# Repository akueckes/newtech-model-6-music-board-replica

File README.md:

# Welcome to another replica project for the Newtech Model 6 Music Board

The Model 6 Music Board from Newtech Computer Systems was launched in 1977 as a low cost alternative to other,
more expensive sound solutions for the S-100 bus like the D+7A from Cromemco.
In contrast to the D+7A with its up to seven bidirectional analog channels, the Newtech board implements just a single audio output channel
and does not provide input channels for e.g. connecting joysticks or keyboards.

The minimalistic design was based on a simple bus interface with address decoder,
a digital to analog converter (DAC) built by a six-step resistor ladder, and a single LM380 IC as simple low power amplifier.

The Music Board can be equipped with a single 2" speaker, or connected to an external amplifier via a phono jack.
Multiple boards can be combined for stereo output.

An optional daughter board can be added to improve the audio quality by an active low pass filter.

Due to the simplistic design, audio generation is achieved by directly and continuously driving the
DAC by the CPU with a constant rate, producing a wave output.
Although this keeps the CPU busy from doing other things, there are no limits concerning the type of audio output.
Music can be produced as well as arbitrary sounds, including human speech or noise.
Multiple voices can be mixed into a single channel, which is then output via the hardware.
Synthesis is just a matter of software, and primarily limited by the performance of the CPU.
Assembler programming, however, is mandatory in order to feed a continuous stream of 6-bit audio samples into the board.

This repository contains the replica KiCAD files for both the Music Board and the low pass filter PCB.
Please consult the Newtech User Manual for a parts list / bill of material.

There are other great replica projects around. The aim of this project is to be as close as possible to the original hardware.
Just a few components need to be added in order to build your own working sound solution for your S-100 based system.

Just as a reference, here is a sample picture of the original hardware without low pass filter

And here a picture of the replica, again without low pass filter, built up with components close to the original

Note that the bus contact fingers of the replica are not gold plated as the original.
Gold plating is a process which needs to be negotiated directly with the PCB producer of your choice and can't be specified by a directive in the Gerber files.

The replica is a nice little project requiring limited budget and skills to create your first own hardware for your personal S-100 system.

This by the way is the very first version of the replica design, please feel free to comment on any kind of improvement,
as long as the replica itself stays as close as possible to the original. A couple of limitations are intentional, so there is for instance
no solder mask in the Gerbers, and no jumper for activating/deactivating the internal speaker,
and as with the original, the low pass filter needs to be added with a daughter board
and is intentionally not integrated into the board design as with other replicas.

For your convenience, a copy of the original Model 6 Music Board user manual is provided,
as well as a BDOS based audio test program I once have written for diverse sound solutions for the S-100 bus,
which also supports up to two Newtech Model 6 Music Boards in parallel. I have created some kind of notation
for playing music scores with multiple channels, an example is the file FANFAR, which works with two boards configured at ports 24H and 28H.
STRINGS and TRUMPS are example wave files which can be loaded for different types of instrumentation.

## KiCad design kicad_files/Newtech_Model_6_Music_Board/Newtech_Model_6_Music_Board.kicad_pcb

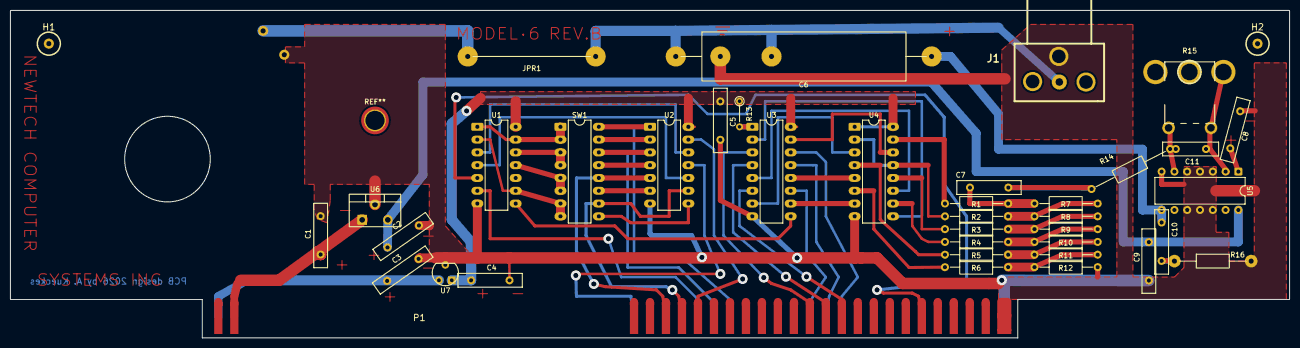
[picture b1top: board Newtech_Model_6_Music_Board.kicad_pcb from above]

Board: 2 copper layers, 254.0 x 65.0 mm, 41 parts (0 on the bottom side), 56 nets.

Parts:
C1, C2, C3: 1uF; C_Disc_D10.0mm_W2.5mm_P300mil
C4, C5, C9, C10: .1; C_Disc_D10.0mm_W2.5mm_P300mil
C6: 220; C_Axial_L22.0mm_D9.5mm_P27.50mm_Horizontal
C7: .1; C_Disc_D10.0mm_W2.5mm_P5.00mm
C8: 4.7; C_Disc_D10.0mm_W2.5mm_P300mil
C11: .0022; C_Disc_D10.0mm_W2.5mm_P6.0mm
H1, H2, H3: Ejector; s100-ejector
J1: RCA_audio_jack
JPR1: R_Axial_DIN0207_L6.3mm_D2.5mm_P15.24mm_Horizontal
P1: S100_MALE
R1, R2, R3, R4, R5, R6: 20K; R_Axial_DIN0207_L6.3mm_D2.5mm_P12.70mm_Horizontal
R7, R8, R9, R10, R11, R12: 10K; R_Axial_DIN0207_L6.3mm_D2.5mm_P12.70mm_Horizontal
R13: 4.7K; R_Axial_DIN0204_L3.6mm_D1.6mm_P5.08mm_Vertical
R14: 2M; R_Axial_DIN0207_L6.3mm_D2.5mm_P15.24mm_Horizontal
R15: 25K; Bourns_3355
R16: 1; R_Axial_DIN0207_L6.3mm_D2.5mm_P15.24mm_Horizontal
SW1: SW_DIP_x08; CERDIP-16_W7.62mm_SideBrazed_LongPads
U1: 74LS30; DIP-14_W7.62mm_LongPads
U2: 74LS04; DIP-14_W7.62mm_LongPads
U3: 74LS174; CERDIP-16_W7.62mm_SideBrazed_LongPads
U4: 4050; CERDIP-16_W7.62mm_SideBrazed_LongPads
U5: LM380N; DIP-14_W7.62mm
U6: LM7812_TO220; TO-220-3_Vertical
U7: L78L05_TO92; TO-92_Inline

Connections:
+8V: C3.1, P1.1 (+8_V), P1.51 (+8_V), U7.3 (VI)
+12V: C2.1, C9.1, U5.14 (VS), U6.3 (VO)
+16V: C1.1, P1.2 (+16_V), U6.1 (VI)
/I/O Enable: U1.8, U3.9 (Cp)
A2: P1.81 (A2), U1.6
A3: P1.31 (A3), U2.13
A4: P1.30 (A4), SW1.10, U2.9
A5: P1.29 (A5), SW1.12, U2.5
A6: P1.82 (A6), SW1.14, U2.3
A7: P1.83 (A7), SW1.16, U2.1
DO2: P1.88 (DO2_ED2), U3.11 (D3)
DO3: P1.89 (DO3_ED3), U3.13 (D4)
DO4: P1.38 (DO4_ED4), U3.3 (D0)
DO5: P1.39 (DO5_ED5), U3.4 (D1)
DO6: P1.40 (DO6_ED6), U3.6 (D2)
DO7: P1.90 (DO7_ED7), U3.14 (D5)
GND: C1.2, C2.2, C3.2, C4.2, C5.2, C8.2, C9.2, J1.2 (Ext), P1.50 (0_V2), P1.100 (0_V5), R12.1, R16.2, U1.7 (GND), U2.7 (GND), U3.8 (GND), U4.8 (VSS), U5.3 (GND), U5.4 (GND), U5.5 (GND), U5.7 (GND), U5.10 (GND), U5.11 (GND), U5.12 (GND), U6.2 (GND), U7.2 (GND)
unnamed: C7.1, R1.1, R7.2
unnamed: C7.2, R14.2
unnamed: C10.1, R16.1
unnamed: C6.1, C10.2, U5.8
unnamed: C6.2, J1.1 (In), JPR1.1 (A)
unnamed: R1.2, U4.15
unnamed: R2.1, R7.1, R8.2
unnamed: R2.2, U4.2
unnamed: R3.1, R8.1, R9.2
unnamed: R3.2, U4.12
unnamed: R4.2, U4.10
unnamed: R5.2, U4.4
unnamed: R6.2, U4.6
unnamed: R5.1, R10.1, R11.2
unnamed: R4.1, R9.1, R10.2
unnamed: R6.1, R11.1, R12.2
unnamed: SW1.1, SW1.2, U1.1, U1.13
unnamed: SW1.3, SW1.4, U1.12
unnamed: SW1.5, SW1.6, U1.11
unnamed: SW1.7, SW1.8, U1.2, U1.9
unnamed: SW1.9, U2.8
unnamed: SW1.11, U2.6
unnamed: SW1.13, U2.4
unnamed: SW1.15, U2.2
unnamed: U1.3, U2.12
unnamed: U1.4, U2.10
unnamed: U3.2 (Q0), U4.9
unnamed: U3.5 (Q1), U4.11
unnamed: U3.7 (Q2), U4.3
unnamed: U3.10 (Q3), U4.7
unnamed: U3.12 (Q4), U4.5
unnamed: U3.15 (Q5), U4.14
unnamed: R13.2, U3.1 (~Mr)
unnamed: C11.2, R15.1, R15.2, U5.2 (+)
unnamed: C11.1, R14.1, R15.3, U5.6 (-)
unnamed: C8.1, U5.1 (BYPASS)
PWR/: P1.77 (pWR*), U2.11
SOUT: P1.45 (sOUT), U1.5
VCC: C4.1, C5.1, R13.1, U1.14 (VCC), U2.14 (VCC), U3.16 (VCC), U4.1 (VCC), U4.16, U7.1 (VO)

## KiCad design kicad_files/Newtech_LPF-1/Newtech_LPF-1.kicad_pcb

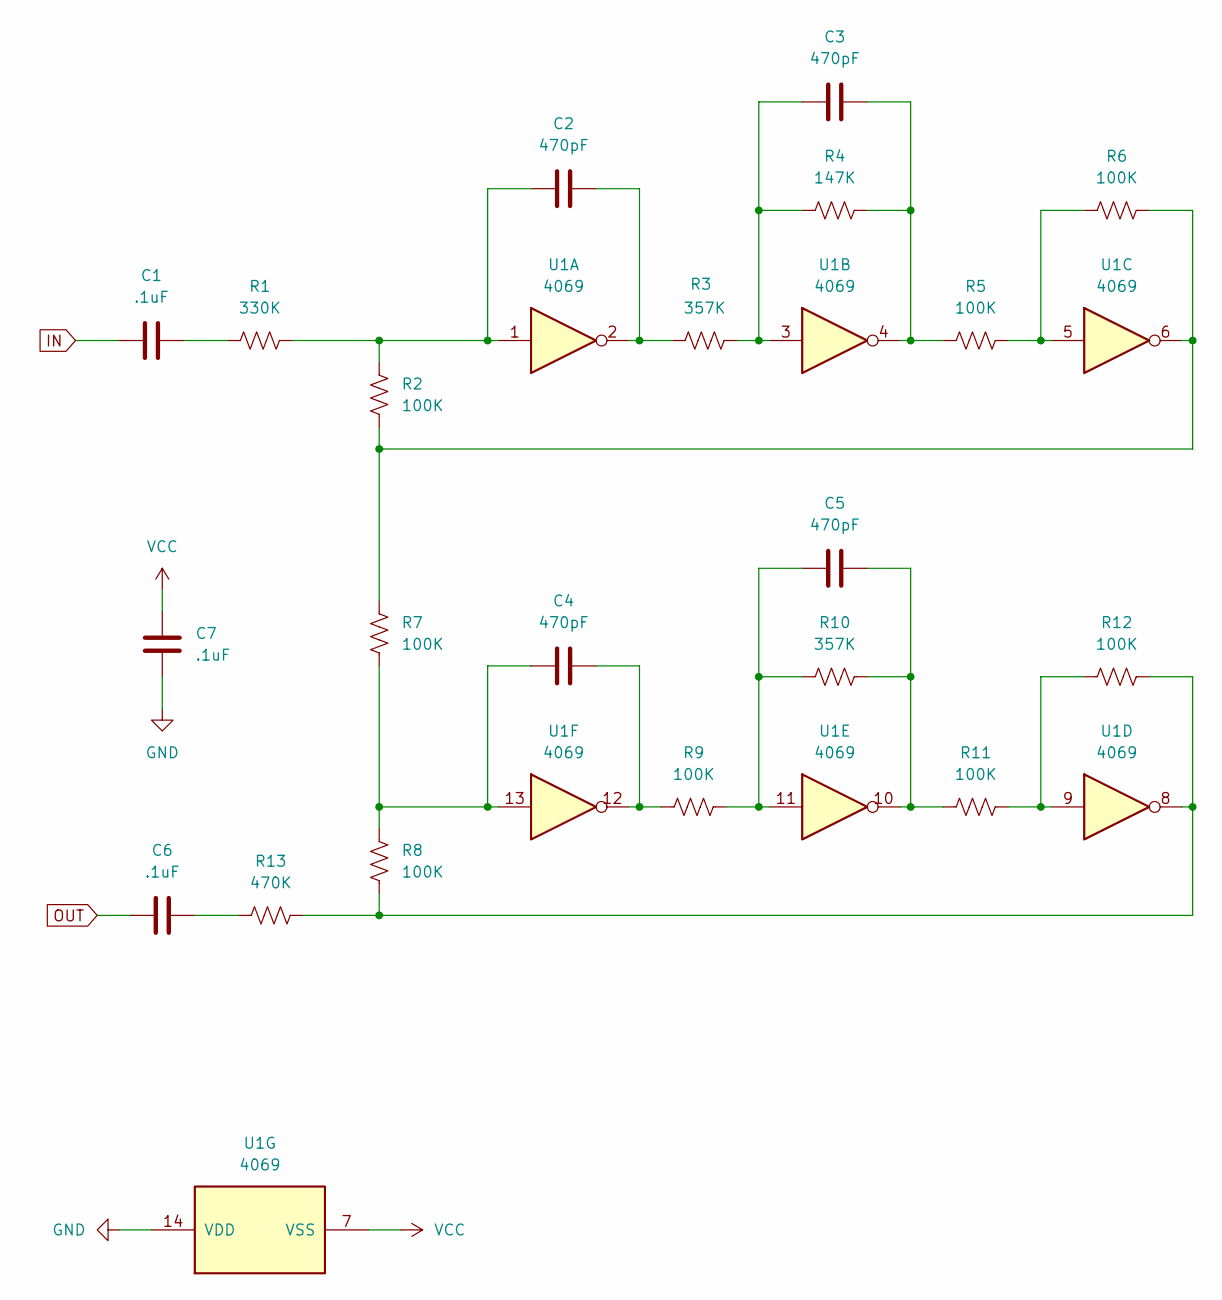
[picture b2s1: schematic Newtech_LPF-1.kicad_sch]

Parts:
C1, C6, C7: .1uF; C_Disc_D10.0mm_W2.5mm_P300mil
C2, C3, C4, C5: 470pF; C_Disc_D10.0mm_W2.5mm_P300mil
R1: 330K; R_Axial_2.5mm_500_mil
R2, R5, R6, R7, R8, R9, R11, R12: 100K; R_Axial_2.5mm_500_mil
R3, R10: 357K; R_Axial_2.5mm_500_mil
R4: 147K; R_Axial_2.5mm_500_mil
R13: 470K; R_Axial_2.5mm_500_mil
U1: 4069; DIP-14_W7.62mm_LongPads

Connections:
GND: C7.2, U1.14 (VDD)
IN: C1.1
unnamed: C1.2, R1.2
unnamed: C2.1, R1.1, R2.1, U1.1
unnamed: C2.2, R3.1, U1.2
unnamed: C3.1, R3.2, R4.1, U1.3
unnamed: C3.2, R4.2, R5.1, U1.4
unnamed: C4.1, R7.2, R8.1, U1.13
unnamed: C4.2, R9.1, U1.12
unnamed: C5.1, R9.2, R10.1, U1.11
unnamed: C5.2, R10.2, R11.1, U1.10
unnamed: C6.2, R13.1
unnamed: R2.2, R6.2, R7.1, U1.6
unnamed: R5.2, R6.1, U1.5
unnamed: R11.2, R12.1, U1.9
unnamed: R8.2, R12.2, R13.2, U1.8
OUT: C6.1
VCC: C7.1, U1.7 (VSS)

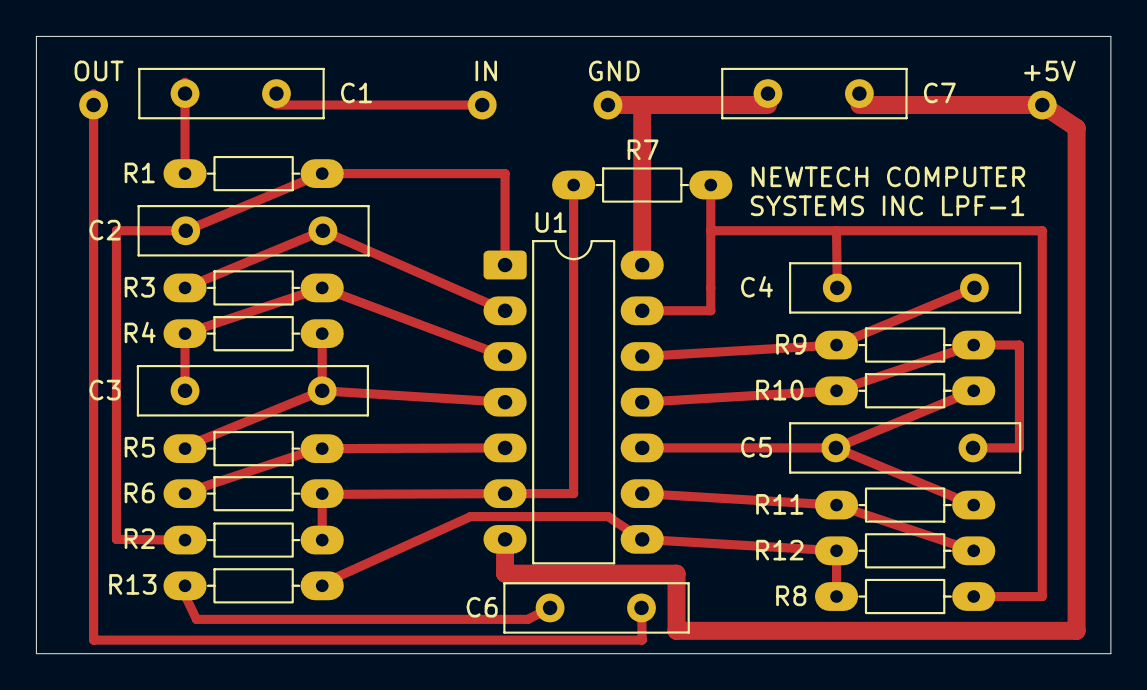
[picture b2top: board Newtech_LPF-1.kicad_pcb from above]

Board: 2 copper layers, 59.7 x 34.3 mm, 21 parts (0 on the bottom side), 16 nets.
